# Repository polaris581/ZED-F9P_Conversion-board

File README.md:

# ZED-F9P_Conversion-board
F9Pをユニバーサル基板上で使うための変換基板です。

二次配布は不可とします。
データの変更についてはご自由にどうぞ！

もし役に立った場合は、Twitterで@polaris581まで連絡をくれると喜びます。

## 使い方
Kicadをインスコ
同梱のP9PのKicadLibraryをKicadに追加。
ファイルを開く。
以上！

## 記事
https://www.mechatronahibi.com/kicad-converter-make/

## 免責事項
本データにより、いかなる損害を被ったとしても責任は負いかねます。

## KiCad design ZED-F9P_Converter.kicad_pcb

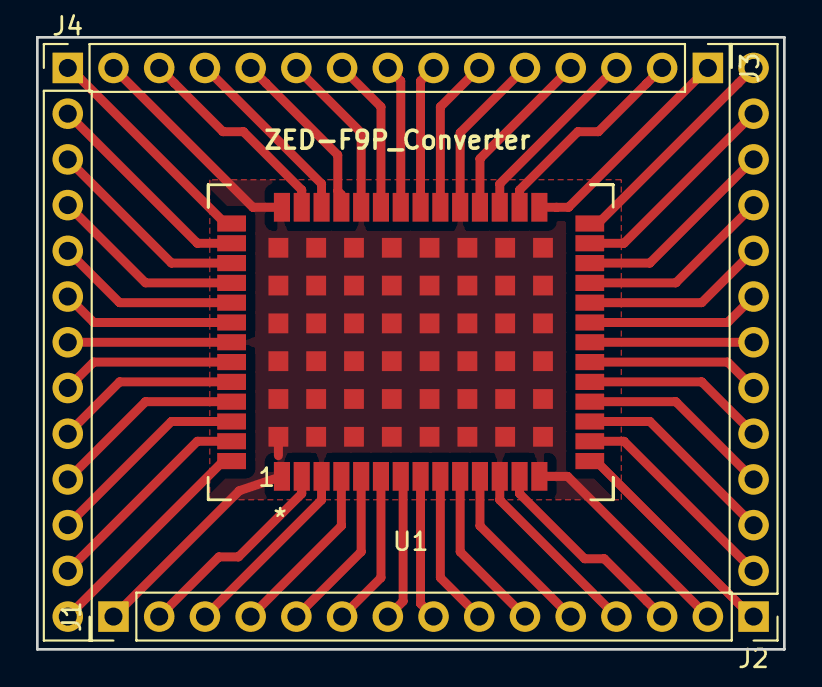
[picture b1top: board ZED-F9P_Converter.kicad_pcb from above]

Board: 2 copper layers, 41.5 x 34.0 mm, 5 parts (0 on the bottom side), 47 nets.

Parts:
J1, J3: Conn_01x14; PinHeader_1x14_P2.54mm_Vertical
J2, J4: Conn_01x13; PinHeader_1x13_P2.54mm_Vertical
U1: Ublox_ZED_F9P; UBLOX_ZED_F9P

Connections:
GND: J1.1, J1.3, J1.12, J1.14, J3.5, J3.10, J3.14, J4.7, U1.0, U1.1, U1.3, U1.12, U1.14, U1.32, U1.37, U1.41, U1.48
unnamed: J1.2, U1.2
unnamed: J1.4, U1.4
unnamed: J1.5, U1.5
unnamed: J1.6, U1.6
unnamed: J1.7, U1.7
unnamed: J1.8, U1.8
unnamed: J1.9, U1.9
unnamed: J1.10, U1.10
unnamed: J1.11, U1.11
unnamed: J1.13, U1.13
unnamed: J2.1, U1.15
unnamed: J2.2, U1.16
unnamed: J2.3, U1.17
unnamed: J2.4, U1.18
unnamed: J2.5, U1.19
unnamed: J2.6, U1.20
unnamed: J2.7, U1.21
unnamed: J2.8, U1.22
unnamed: J2.9, U1.23
unnamed: J2.10, U1.24
unnamed: J2.11, U1.25
unnamed: J2.12, U1.26
unnamed: J2.13, U1.27
unnamed: J3.1, U1.28
unnamed: J3.2, U1.29
unnamed: J3.3, U1.30
unnamed: J3.4, U1.31
unnamed: J3.6, U1.33
unnamed: J3.7, U1.34
unnamed: J3.8, U1.35
unnamed: J3.9, U1.36
unnamed: J3.11, U1.38
unnamed: J3.12, U1.39
unnamed: J3.13, U1.40
unnamed: J4.1, U1.42
unnamed: J4.2, U1.43
unnamed: J4.3, U1.44
unnamed: J4.4, U1.45
unnamed: J4.5, U1.46
unnamed: J4.6, U1.47
unnamed: J4.8, U1.49
unnamed: J4.9, U1.50
unnamed: J4.10, U1.51
unnamed: J4.11, U1.52
unnamed: J4.12, U1.53
unnamed: J4.13, U1.54

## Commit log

2020-04-05 ファイルを追加
2020-04-05 Add Library
2020-04-06 線幅0.5mmに変更
2020-04-09 軽微な変更
